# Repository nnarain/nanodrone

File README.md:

# nanodrone

A mini drone based on an Arduino Nano BLE 33 Sense

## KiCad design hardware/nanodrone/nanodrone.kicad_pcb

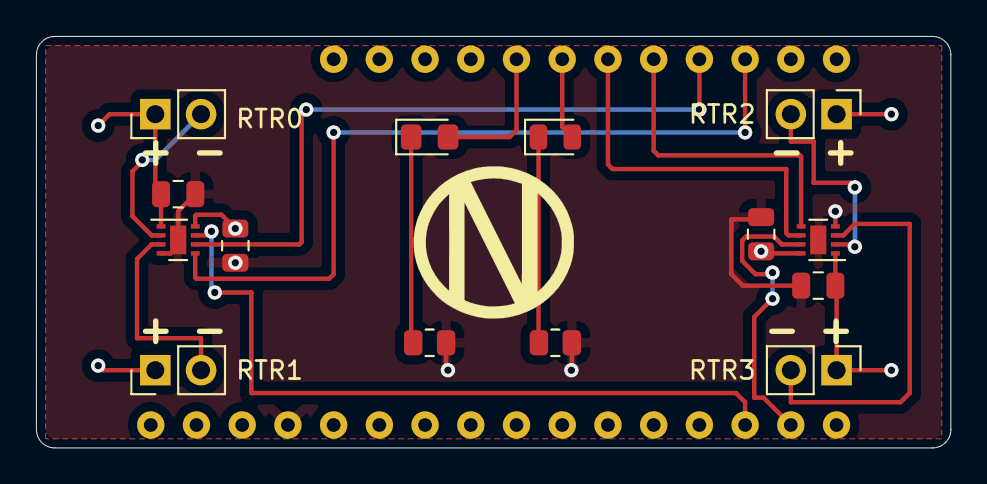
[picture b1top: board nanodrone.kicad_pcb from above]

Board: 4 copper layers, 50.8 x 22.9 mm, 15 parts (0 on the bottom side), 17 nets.

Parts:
C1, C2, C3, C4: 100nF; C_0805_2012Metric
D1: DGB1; LED_0805_2012Metric
D2: DBG2; LED_0805_2012Metric_Pad1.15x1.40mm_HandSolder
J1: RTR0; PinHeader_1x02_P2.54mm_Vertical
J2: RTR1; PinHeader_1x02_P2.54mm_Vertical
J3: RTR2; PinHeader_1x02_P2.54mm_Vertical
J4: RTR3; PinHeader_1x02_P2.54mm_Vertical
R7, R10: 100; R_0805_2012Metric
U1: Feather; Feather_no_mounting
U2, U3: DRV8837; WSON-8-1EP_2x2mm_P0.5mm_EP0.9x1.6mm

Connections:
+3V3: C1.1, C3.1, U1.14 (VCC), U2.8 (VCC), U3.8 (VCC)
+BATT: C2.1, C4.1, J1.1, J2.1, J3.1, J4.1, U1.1 (VBAT), U2.1 (VM), U3.1 (VM)
/dbg1: D1.2 (A), U1.6 (D11)
/dbg2: D2.2 (A), U1.5 (D12)
/drv_en1: U1.26 (D0), U2.7 (~SLEEP)
/drv_en2: U1.27 (D1), U3.7 (~SLEEP)
/rtr0: J1.2, U2.2 (OUT1)
/rtr1: J2.2, U2.3 (OUT2)
/rtr2: J3.2, U3.2 (OUT1)
/rtr3: J4.2, U3.3 (OUT2)
/rtrctl0: U1.10 (D5), U2.5 (IN2)
/rtrctl1: U1.9 (D6), U2.6 (IN1)
/rtrctl2: U1.8 (D9), U3.5 (IN2)
/rtrctl3: U1.7 (D10), U3.6 (IN1)
GND: C1.2, C2.2, C3.2, C4.2, R7.2, R10.2, U1.16 (GND), U2.4 (GND), U2.9 (GND), U3.4 (GND), U3.9 (GND)
unnamed: D1.1 (K), R7.1
unnamed: D2.1 (K), R10.1

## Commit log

2021-09-12 Initial design
2021-10-04 Fix pwm connection. Add jlcpcb part numbers
2021-10-05 Update BOM and plots
2021-11-19 Rev C
2022-02-16 Rev D
2022-03-26 rev E
2022-03-26 kibot config
2022-04-07 kibot bom config
